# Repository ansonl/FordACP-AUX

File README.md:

# Ford CD changer emulator with AUX audio and stock playback control using Arduino UNO

### **Keep the retro stereo. Bring your own tunes.**

Add AUX audio input to your older Ford vehicle using a Atmega328 (Arduino UNO) and use the stock radio head unit to control playback on your iPhone. 

## [Read about the development of this.](http://ansonliu.com/2017/09/ford-acp-cd-changer-emulator-aux-audio/)

  - Adapted from Dale Thomas's [*Ford Bluetooth Interface*](http://www.instructables.com/id/Ford-Bluetooth-Interface-Control-phone-with-stock-/) and Krysztof Pintscher's  [Ford CD Emulator](http://www.instructables.com/id/Ford-CD-Emulator-Arduino-Mega/).
  - Uses Ford Audio Control Protocol (ACP) to emulate stock 6 CD Changer.
  - Adds AUX audio input to vehicle.
  - Allows stock head unit playback control of iPhone.
  - Protoshield hand wiring diagram included in `Resources` folder. 
  - EAGLE PCB files in `eagle` folder.

### Directions
  - Open **Ford_ACP_AUX.ino** located in *Sketch/Ford_ACP_AUX* and upload to Arduino UNO.
  - Acquire parts on Bill of Materials located in *Resources/LIU_FORD_ACP_AUX_BOM.xlsx*.
  - Do one of the following
    1. Wire up Arduino UNO like shown below. *Note: Updated pin 8 → pin 7 in latest code.*
    2. Print PCB using provided EAGLE files.
  - Place the assembly in your car.

#### BLE vehicle lock/unlock.
  - Follow directions above but use **Ford_AUX_BLE_control.ino** located in *Sketch/Ford_AUX_BLE_control* and upload to Arduino UNO.
  - Build and install [ansonl/ble-control](https://github.com/ansonl/ble-control) on your iOS device.

*Please note that pin 8 in the above diagram has been changed to pin 7 in the latest Ford_AUX_BLE code.* 

#### ACP Data Logging and LCD Graphing
  - Use **Ford_LCD_datagraph.ino** located in *Sketch/Ford_LCD_datagraph*.

### Contributing

Please report issues and submit pull requests as needed. Please make an issue for soldering or build issues, too. 

I have resolved several people's build issues by email and someone may find your issue helpful!

### License

Any adaptation of this work must comply with licenses of previous works (those in `Resources` folder) and include references to the previous authors. 

**Any work by Anson Liu in this repository is under MIT License.**

  - Andrew Hammond
  - [Krysztof Pintscher](http://www.instructables.com/id/Ford-CD-Emulator-Arduino-Mega/)
  - [Dale Thomas](http://www.instructables.com/id/Ford-Bluetooth-Interface-Control-phone-with-stock-/)
  - [Anson Liu](http://ansonliu.com)

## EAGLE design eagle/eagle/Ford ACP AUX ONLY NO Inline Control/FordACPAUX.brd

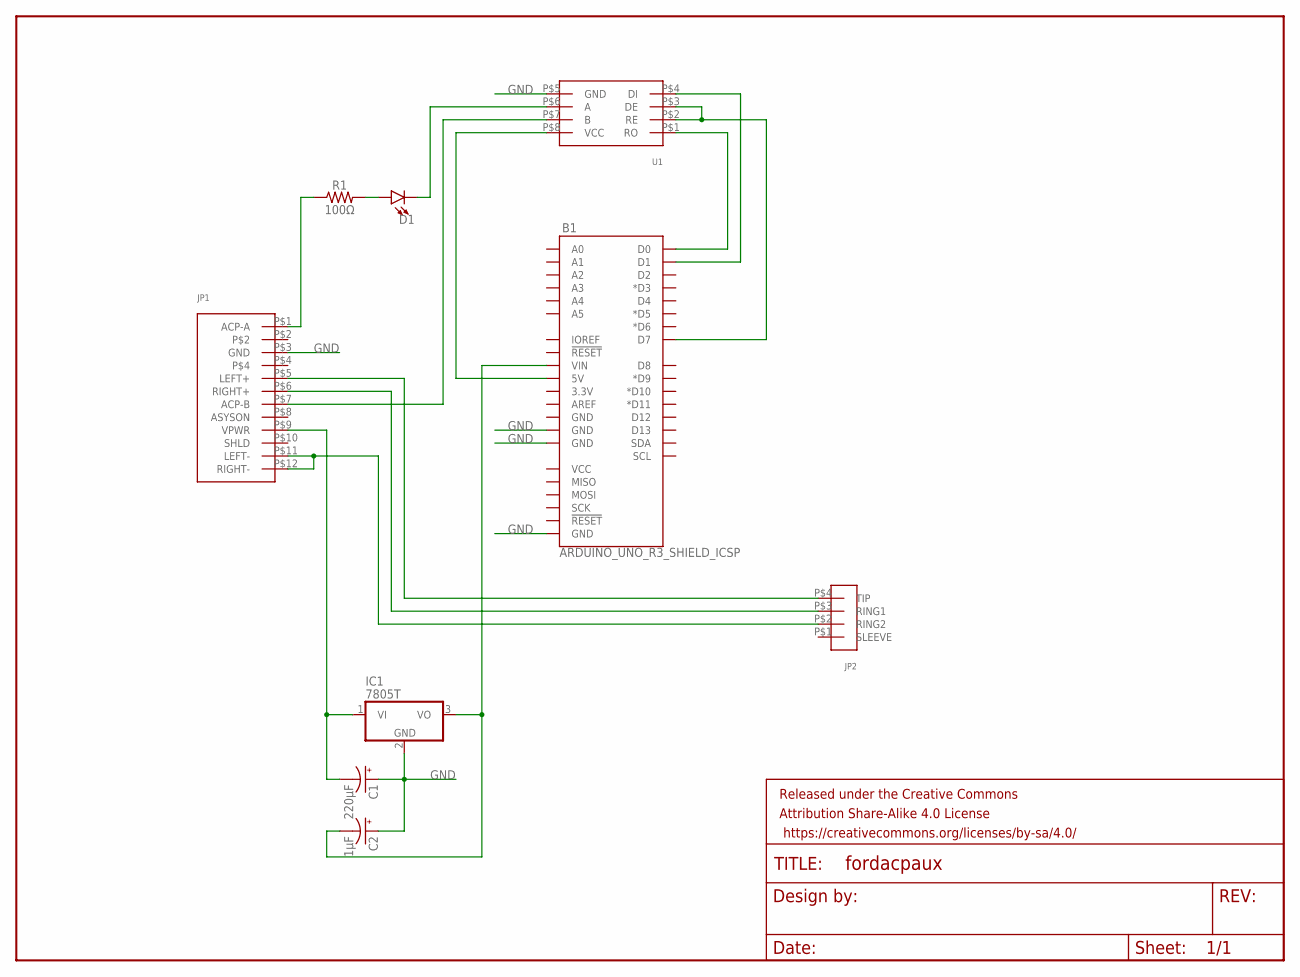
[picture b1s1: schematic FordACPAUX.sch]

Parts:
B1: ARDUINO_UNO_R3_SHIELD_ICSP; UNO_R3_SHIELD_ICSP
C1: 220μF; E2,5-7
C2: 1μF; E2-4
D1: LED3MM; LED_3MM
FRAME1: FRAME-LETTER; CREATIVE_COMMONS
IC1: 7805T; TO220H
JP1: AMP-174051-2_040_MULTILOCK; AMP_174051-2_040_MULTILOCK
JP2: TRRS_JACKBREAKOUT; HEADER-4-PIN-TRRS-JACK-BREAKOUT
R1: 100Ω; AXIAL-0.3
U1: MAX485_TTL_TO_RS_485_MODULE

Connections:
GND: B1.GND@0 (GND), B1.GND@1 (GND), B1.GND_ICSP (GND), C1.+, C2.+, IC1.2 (GND), JP1.P$3 (GND), U1.P$5 (GND)
unnamed: JP1.P$1 (ACP-A), R1.P$1 (1)
unnamed: JP1.P$7 (ACP-B), U1.P$7 (B)
unnamed: D1.A, R1.P$2 (2)
unnamed: D1.K (C), U1.P$6 (A)
unnamed: C1.-, IC1.1 (VI), JP1.P$9 (VPWR)
unnamed: B1.5V, U1.P$8 (VCC)
unnamed: B1.D7, U1.P$2 (RE), U1.P$3 (DE)
unnamed: B1.RX (D0), U1.P$1 (RO)
unnamed: B1.TX (D1), U1.P$4 (DI)
unnamed: JP1.P$5 (LEFT+), JP2.P$4 (TIP)
unnamed: JP1.P$6 (RIGHT+), JP2.P$3 (RING1)
unnamed: JP1.P$11 (LEFT-), JP1.P$12 (RIGHT-), JP2.P$2 (RING2)
unnamed: B1.VIN, C2.-, IC1.3 (VO)

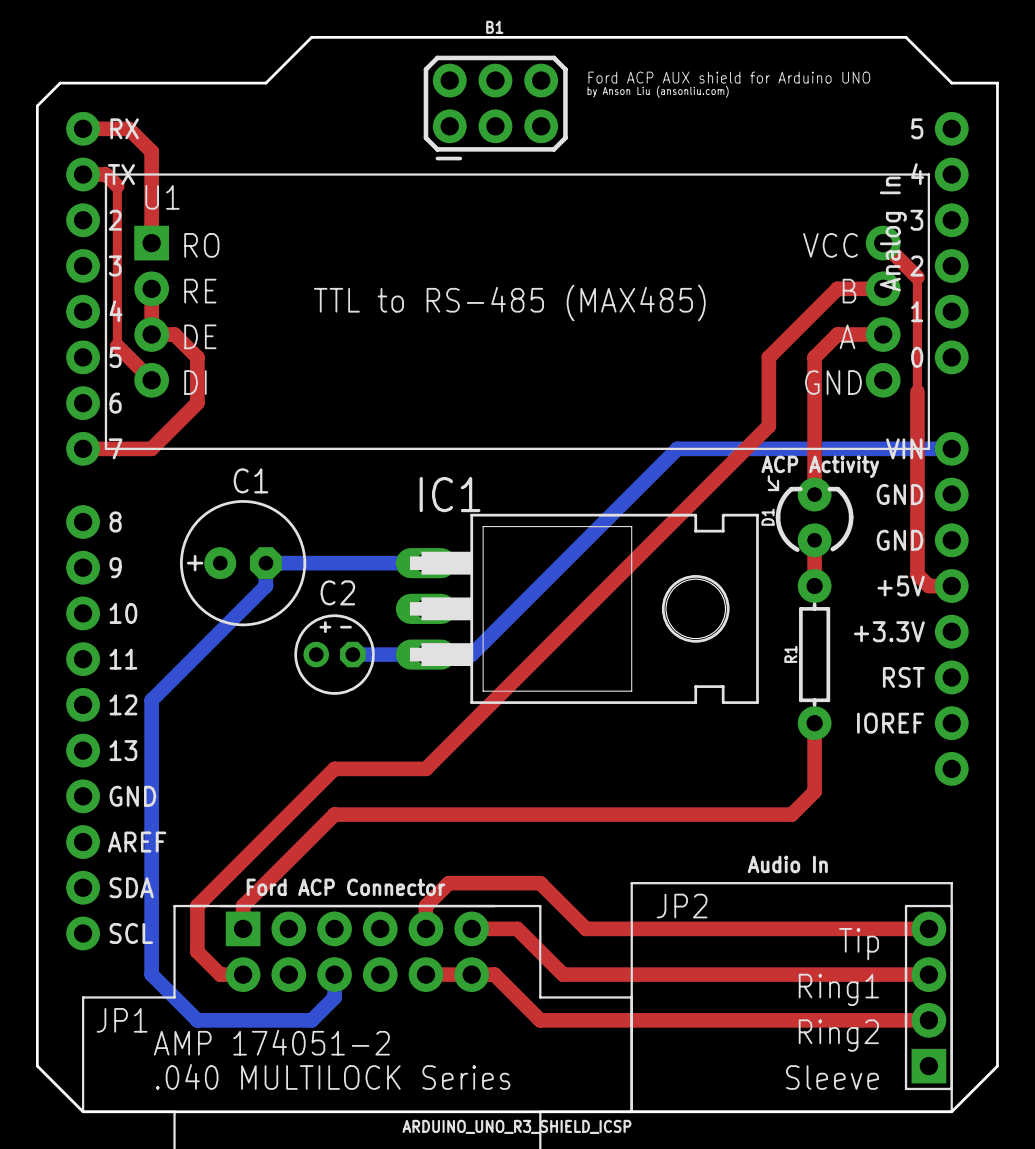
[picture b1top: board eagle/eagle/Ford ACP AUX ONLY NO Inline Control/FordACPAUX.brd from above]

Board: 2 copper layers, 53.3 x 59.7 mm, 10 parts (0 on the bottom side), 14 nets.

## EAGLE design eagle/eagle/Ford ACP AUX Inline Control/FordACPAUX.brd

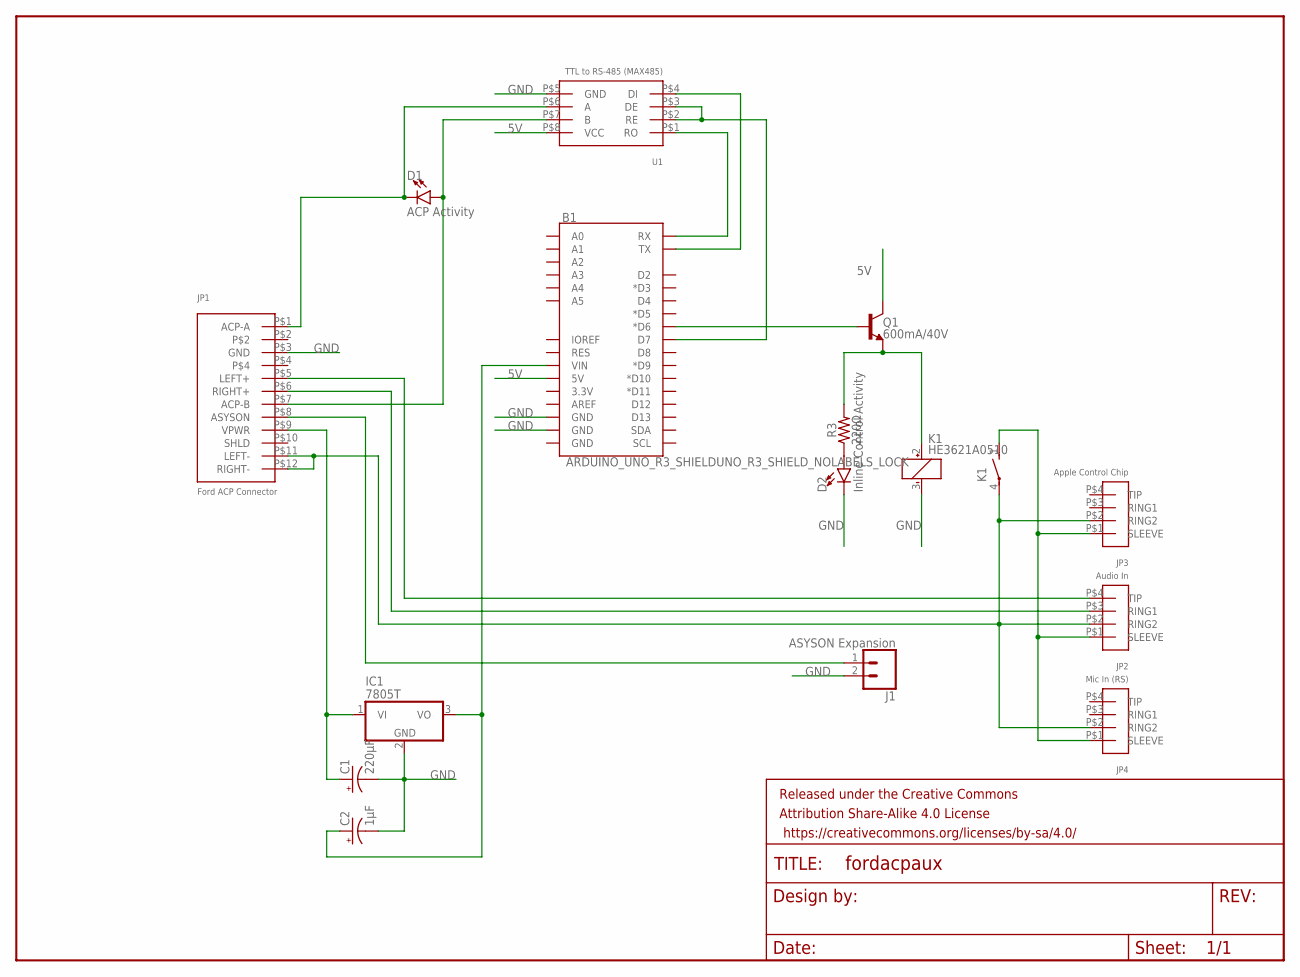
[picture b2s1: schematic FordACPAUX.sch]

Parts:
B1: ARDUINO_UNO_R3_SHIELDUNO_R3_SHIELD_NOLABELS_LOCK; UNO_R3_SHIELD_NOLABELS_LOCK
C1: 220μF; E2,5-7
C2: 1μF; E2-4
D1: ACP Activity; LED_3MM
D2: Inline Control Activity; LED_3MM
FRAME1: FRAME-LETTERNO_PACKAGE; DUMMY
IC1: 7805T; TO220H
J1: ASYSON Expansion; 1X02_LOCK
JP1: Ford ACP Connector; AMP_174051-2_040_MULTILOCK
JP2: Audio In; 3-5MM_4_POLE_TRRS_PCB_MOUNT
JP3: Apple Control Chip; 3-5MM_4_POLE_TRRS_PCB_MOUNT
JP4: Mic In (RS); 3-5MM_4_POLE_TRRS_PCB_MOUNT
K1: HE3621A0510; HE3621
Q1: 600mA/40V; TO-92
R3: 220Ω; AXIAL-0.3
U1: TTL to RS-485 (MAX485); MAX485_TTL_TO_RS_485_MODULE

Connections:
5V: B1.5V, Q1.1 (C), U1.P$8 (VCC)
GND: B1.GND@1 (GND), B1.GND@2 (GND), C1.-, C2.-, D2.K (C), IC1.2 (GND), J1.2, JP1.P$3 (GND), K1.3 (-), U1.P$5 (GND)
unnamed: D1.A, JP1.P$7 (ACP-B), U1.P$7 (B)
unnamed: D1.K (C), JP1.P$1 (ACP-A), U1.P$6 (A)
unnamed: C1.+, IC1.1 (VI), JP1.P$9 (VPWR)
unnamed: B1.D6 (*D6), Q1.2 (B)
unnamed: B1.D7, U1.P$2 (RE), U1.P$3 (DE)
unnamed: K1.2 (+), Q1.3 (E), R3.P$2 (2)
unnamed: B1.RX, U1.P$1 (RO)
unnamed: B1.TX, U1.P$4 (DI)
unnamed: JP1.P$5 (LEFT+), JP2.P$4 (TIP)
unnamed: JP1.P$6 (RIGHT+), JP2.P$3 (RING1)
unnamed: JP1.P$11 (LEFT-), JP1.P$12 (RIGHT-), JP2.P$2 (RING2), JP3.P$2 (RING2), JP4.P$2 (RING2), K1.4
unnamed: JP2.P$1 (SLEEVE), JP3.P$1 (SLEEVE), JP4.P$1 (SLEEVE), K1.1 (S)
unnamed: B1.VIN, C2.+, IC1.3 (VO)
unnamed: D2.A, R3.P$1 (1)
unnamed: J1.1, JP1.P$8 (ASYSON)

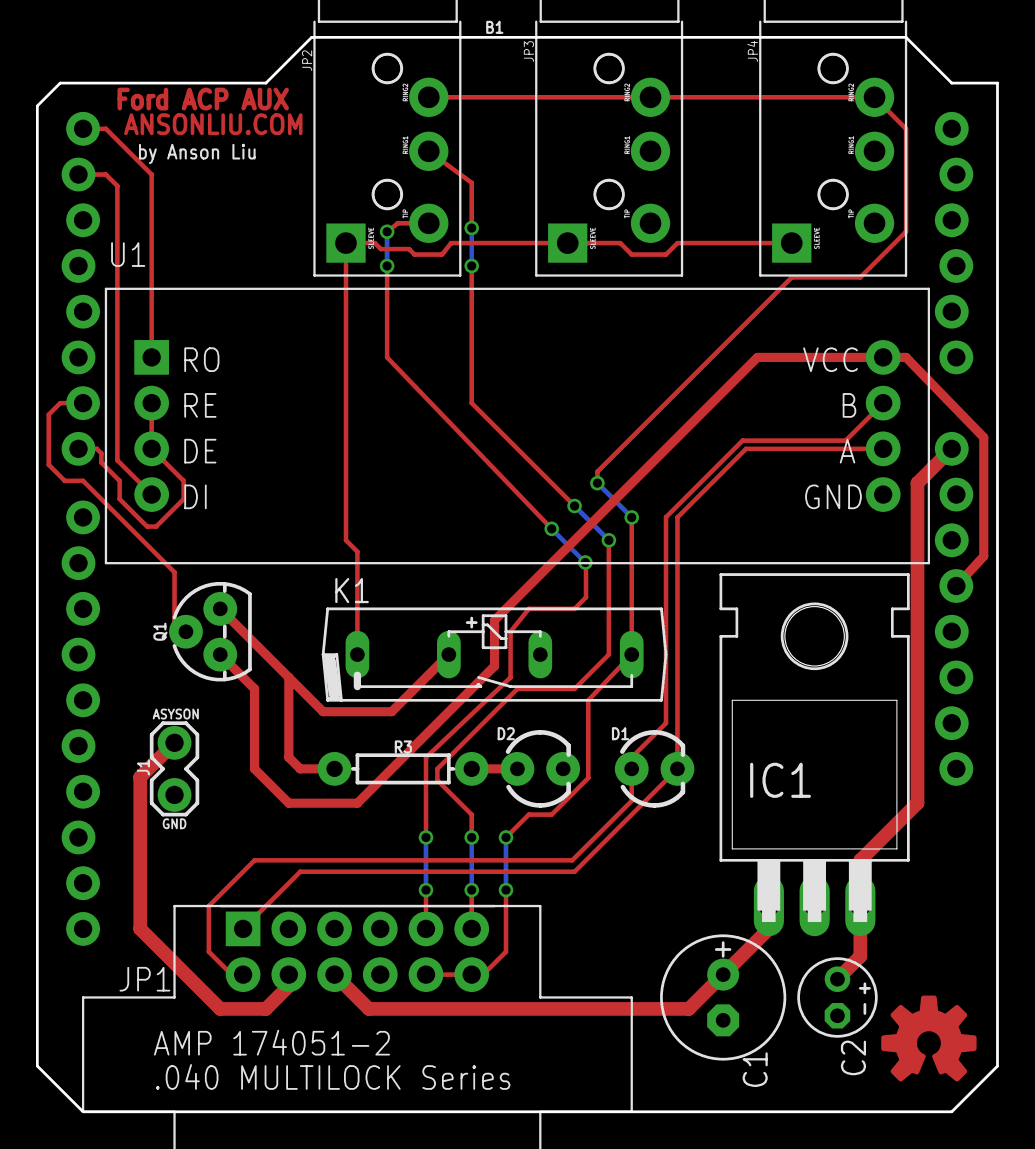
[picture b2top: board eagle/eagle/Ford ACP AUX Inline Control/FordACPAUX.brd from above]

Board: 2 copper layers, 53.3 x 59.7 mm, 17 parts (0 on the bottom side), 17 nets.

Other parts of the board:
U$1: OSHWLOGO_TOP_0.2

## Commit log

2017-05-08 add README
2017-05-08 Update naming
2017-06-17 aux inline control working
2017-08-05 work in progress, logging ACP data for energy info
2017-08-17 lcd graphs
2017-08-18 added 74hc595 hd44780 bargraph of energy info
2017-08-29 ford ble control in progress
2017-09-01 working on eeprom test
2017-09-11 work in proress on ble control
2017-09-17 add license
2017-09-17 edit README for BLE control
2017-09-17 fix link in README
2017-09-17 add BOM
2017-09-24 Add directory for SD datalogging RX only sketch Fixed minutes:seconds play time display in ACP.ino Ford_AUX_BLE_control sketch (latest branch
2017-09-25 change minutes:seconds variable to uint8_t to prevent overflow in acp_tx array
2017-12-08 Add standalone ACP AUX control version of code with BLE control removed available in Sketch/Ford_ACP_AUX
2017-12-08 updated notes for clarity

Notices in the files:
parts and their libraries:
SparkFun-Boards: Licensing: Creative Commons ShareAlike 4.0 International - https://creativecommons.org/licenses/by-sa/4.0
SparkFun-Aesthetics: Released under the Creative Commons Attribution Share-Alike 4.0 License
SparkFun-Aesthetics: https://creativecommons.org/licenses/by-sa/4.0
